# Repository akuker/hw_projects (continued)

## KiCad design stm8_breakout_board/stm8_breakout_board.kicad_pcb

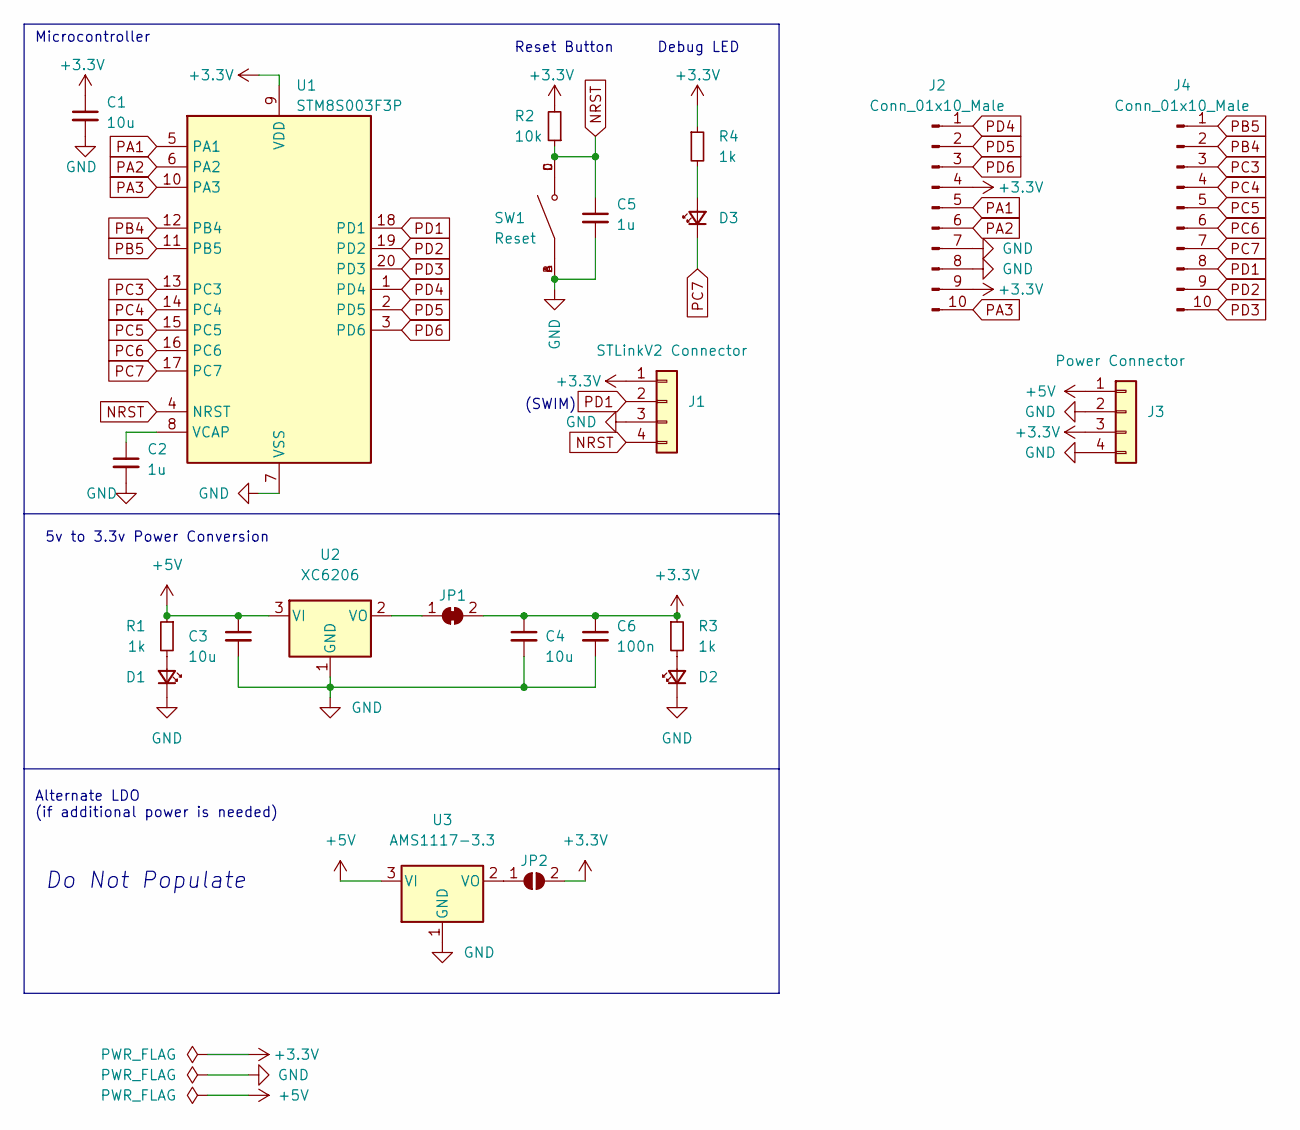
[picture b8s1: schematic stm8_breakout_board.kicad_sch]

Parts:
C1, C3, C4: 10u; C_0603_1608Metric; LCSC C19702
C2, C5: 1u; C_0603_1608Metric; LCSC C15849
C6: 100n; C_0603_1608Metric; LCSC C14663
D1: 5v; LED_0603_1608Metric; LCSC C72043
D2: 3.3v; LED_0603_1608Metric; LCSC C72043
D3: PC7; LED_0603_1608Metric; LCSC C72043
J1: STLinkV2 Connector; PinHeader_1x04_P2.54mm_Vertical; LCSC DNP
J2, J4: Conn_01x10_Male; PinHeader_1x10_P2.54mm_Vertical; LCSC DNP
J3: Power Connector; PinHeader_1x04_P2.54mm_Vertical; LCSC DNP
JP1: SolderJumper_2_Bridged; SolderJumper-2_P1.3mm_Bridged_RoundedPad1.0x1.5mm; LCSC DNP
JP2: SolderJumper_2_Bridged; SolderJumper-2_P1.3mm_Open_RoundedPad1.0x1.5mm; LCSC DNP
R1, R3, R4: 1k; R_0603_1608Metric; LCSC C21190
R2: 10k; R_0603_1608Metric; LCSC C25804
SW1: Reset; SW_TS-1187A-B-A-B; PARTREV A0; LCSC C318884
U1: STM8S003F3P; TSSOP-20_4.4x6.5mm_P0.65mm; LCSC C52717
U2: XC6206; SOT-23; LCSC C5446
U3: AMS1117-3.3; SOT-223-3_TabPin2; LCSC C6186

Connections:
+3V3: C1.1, C4.1, C6.1, J1.1, J2.4, J2.9, J3.3, JP1.2 (B), JP2.2 (B), R2.2, R3.1, R4.1, U1.9 (VDD)
+5V: C3.1, J3.1, R1.1, U2.3 (VI), U3.3 (VI)
GND: C1.2, C2.2, C3.2, C4.2, C5.2, C6.2, D1.1 (K), D2.1 (K), J1.3, J2.7, J2.8, J3.2, J3.4, SW1.A, SW1.B, U1.7 (VSS), U2.1 (GND), U3.1 (GND)
NRST: C5.1, J1.4, R2.1, SW1.C, SW1.D, U1.4 (NRST)
unnamed: C2.1, U1.8 (VCAP)
unnamed: D1.2 (A), R1.2
unnamed: D2.2 (A), R3.2
unnamed: D3.2 (A), R4.2
unnamed: JP1.1 (A), U2.2 (VO)
unnamed: JP2.1 (A), U3.2 (VO)
PA1: J2.5, U1.5 (PA1)
PA2: J2.6, U1.6 (PA2)
PA3: J2.10, U1.10 (PA3)
PB4: J4.2, U1.12 (PB4)
PB5: J4.1, U1.11 (PB5)
PC3: J4.3, U1.13 (PC3)
PC4: J4.4, U1.14 (PC4)
PC5: J4.5, U1.15 (PC5)
PC6: J4.6, U1.16 (PC6)
PC7: D3.1 (K), J4.7, U1.17 (PC7)
PD1: J1.2, J4.8, U1.18 (PD1)
PD2: J4.9, U1.19 (PD2)
PD3: J4.10, U1.20 (PD3)
PD4: J2.1, U1.1 (PD4)
PD5: J2.2, U1.2 (PD5)
PD6: J2.3, U1.3 (PD6)

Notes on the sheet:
Reset Button
Debug LED
5v to 3.3v Power Conversion
Do Not Populate
Alternate LDO (if additional power is needed)
(SWIM)
Microcontroller

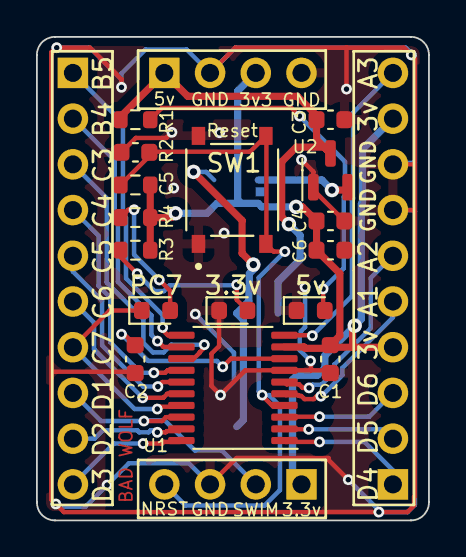
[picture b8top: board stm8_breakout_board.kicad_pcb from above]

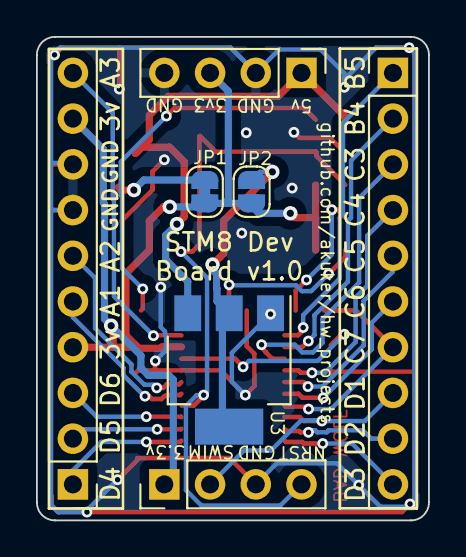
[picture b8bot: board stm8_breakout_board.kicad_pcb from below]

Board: 2 copper layers, 21.8 x 26.9 mm, 23 parts (7 on the bottom side), 26 nets.
